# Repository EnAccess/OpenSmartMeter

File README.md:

<p align="center">
  
</p>
<p align="center">
    <em>The Open Smart Meter solves a problem that affects most solar developers in the industry. This inexpensive and open source Smart Meter meets IEC and key elements of the local regulations in Nigeria.</em>
</p>
<p align="center">

</p>

---

## Description

This repository contains manufacturing details as related to smart energy meter, details such as hardware design, web software, firmware, exterior casing STL files, rationale behing design, how-to document to guide a skilled user to replicate every part of the smart meter is available in the repository.

## Technical developmental breakdown

The open-source smart meter development has four main parts to it as highlighted below:

### Circuit and Enclosure Design

The circuit was designed on Kicad free and open-source PCB design software while the enclosure design was done using Fusion 360 software.

### PCB and Enclosure fabrication

PCB fabrication involves putting together the physical components that makes up the smart meter.
The PCB features a 2layer design incorporating CICADA GSM module for communication while the enclosure offers a minimalistic IP 51 design according to IEC metering enclosure design standard.

### Firmware, Web interface Development & API integration

The firmware code was written in Arduino IDE using C++, while the web front end was written majorly in HTML and CSS while the back end was written majorly in PHP.
Links to all these codes are here.
ThingsBoard API was used to view meter parameters such as energy, credit.

### Calibration & Testing

After putting the hardware and software together, we needed to validate the performance of the smart meter and ascertain its accuracy.
Due to varying tolerances of used components, it is vital to perform a calibration exercise.
This is used to correct any errors due to varying tolerances.
Further details including source code, schematics, and manufacturing files can be found in the EnAccess github repository

### Infrastructure diagram

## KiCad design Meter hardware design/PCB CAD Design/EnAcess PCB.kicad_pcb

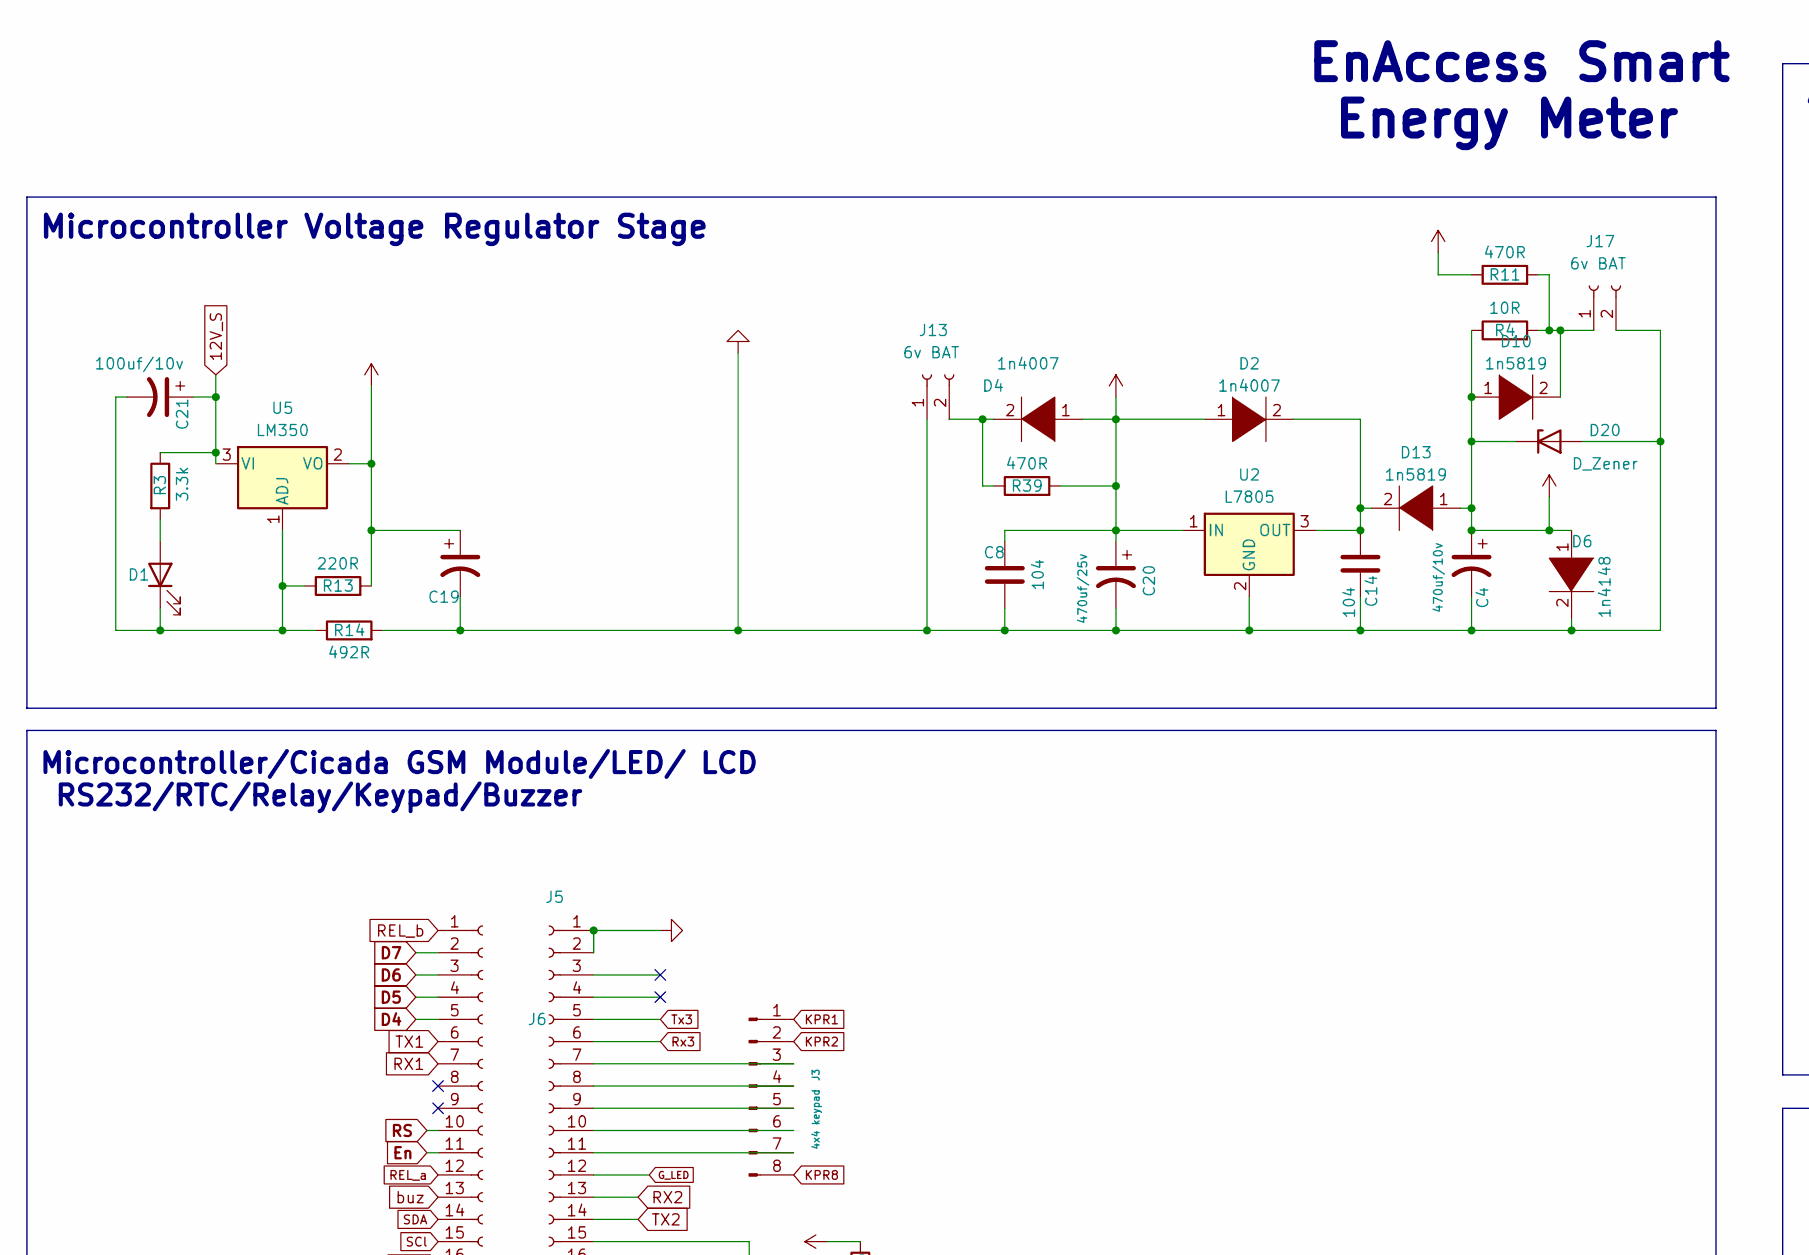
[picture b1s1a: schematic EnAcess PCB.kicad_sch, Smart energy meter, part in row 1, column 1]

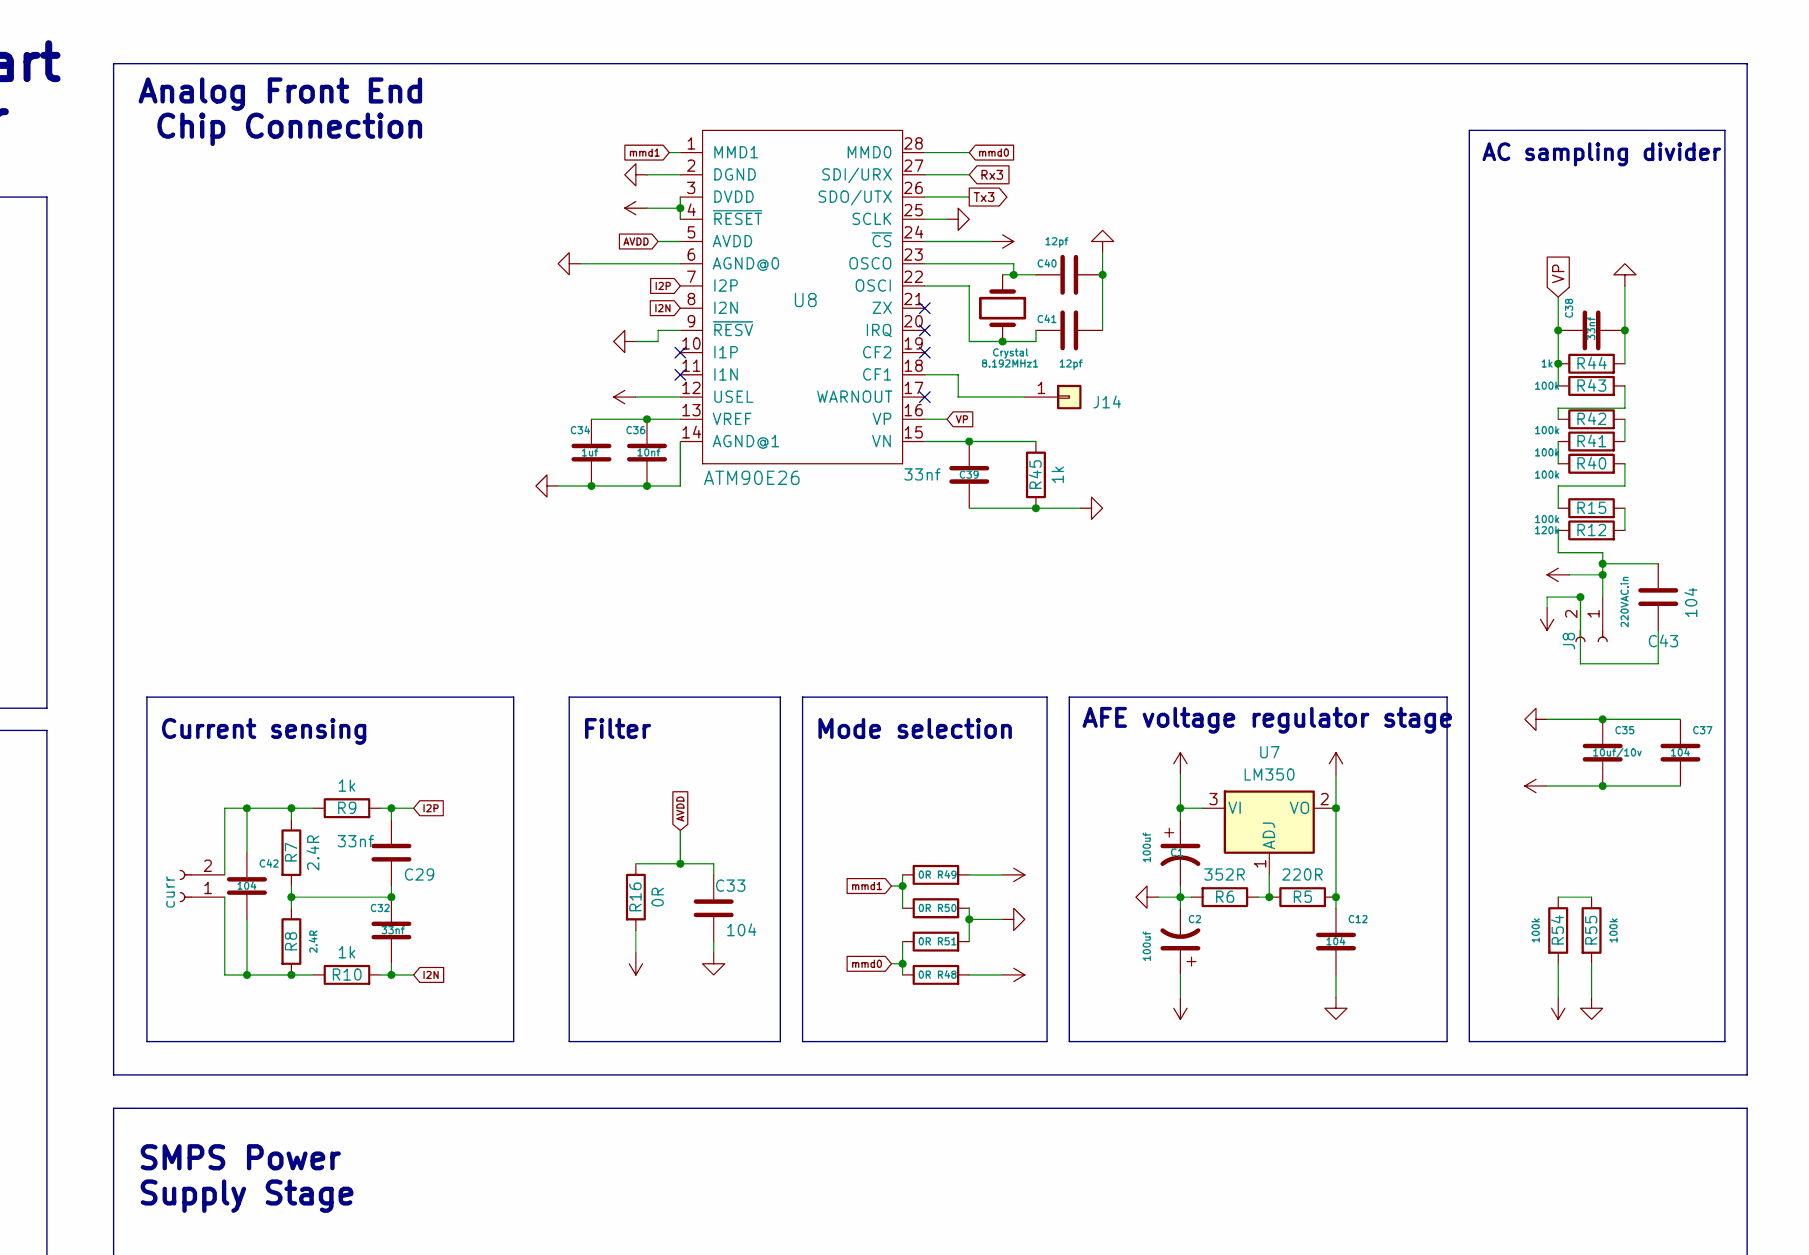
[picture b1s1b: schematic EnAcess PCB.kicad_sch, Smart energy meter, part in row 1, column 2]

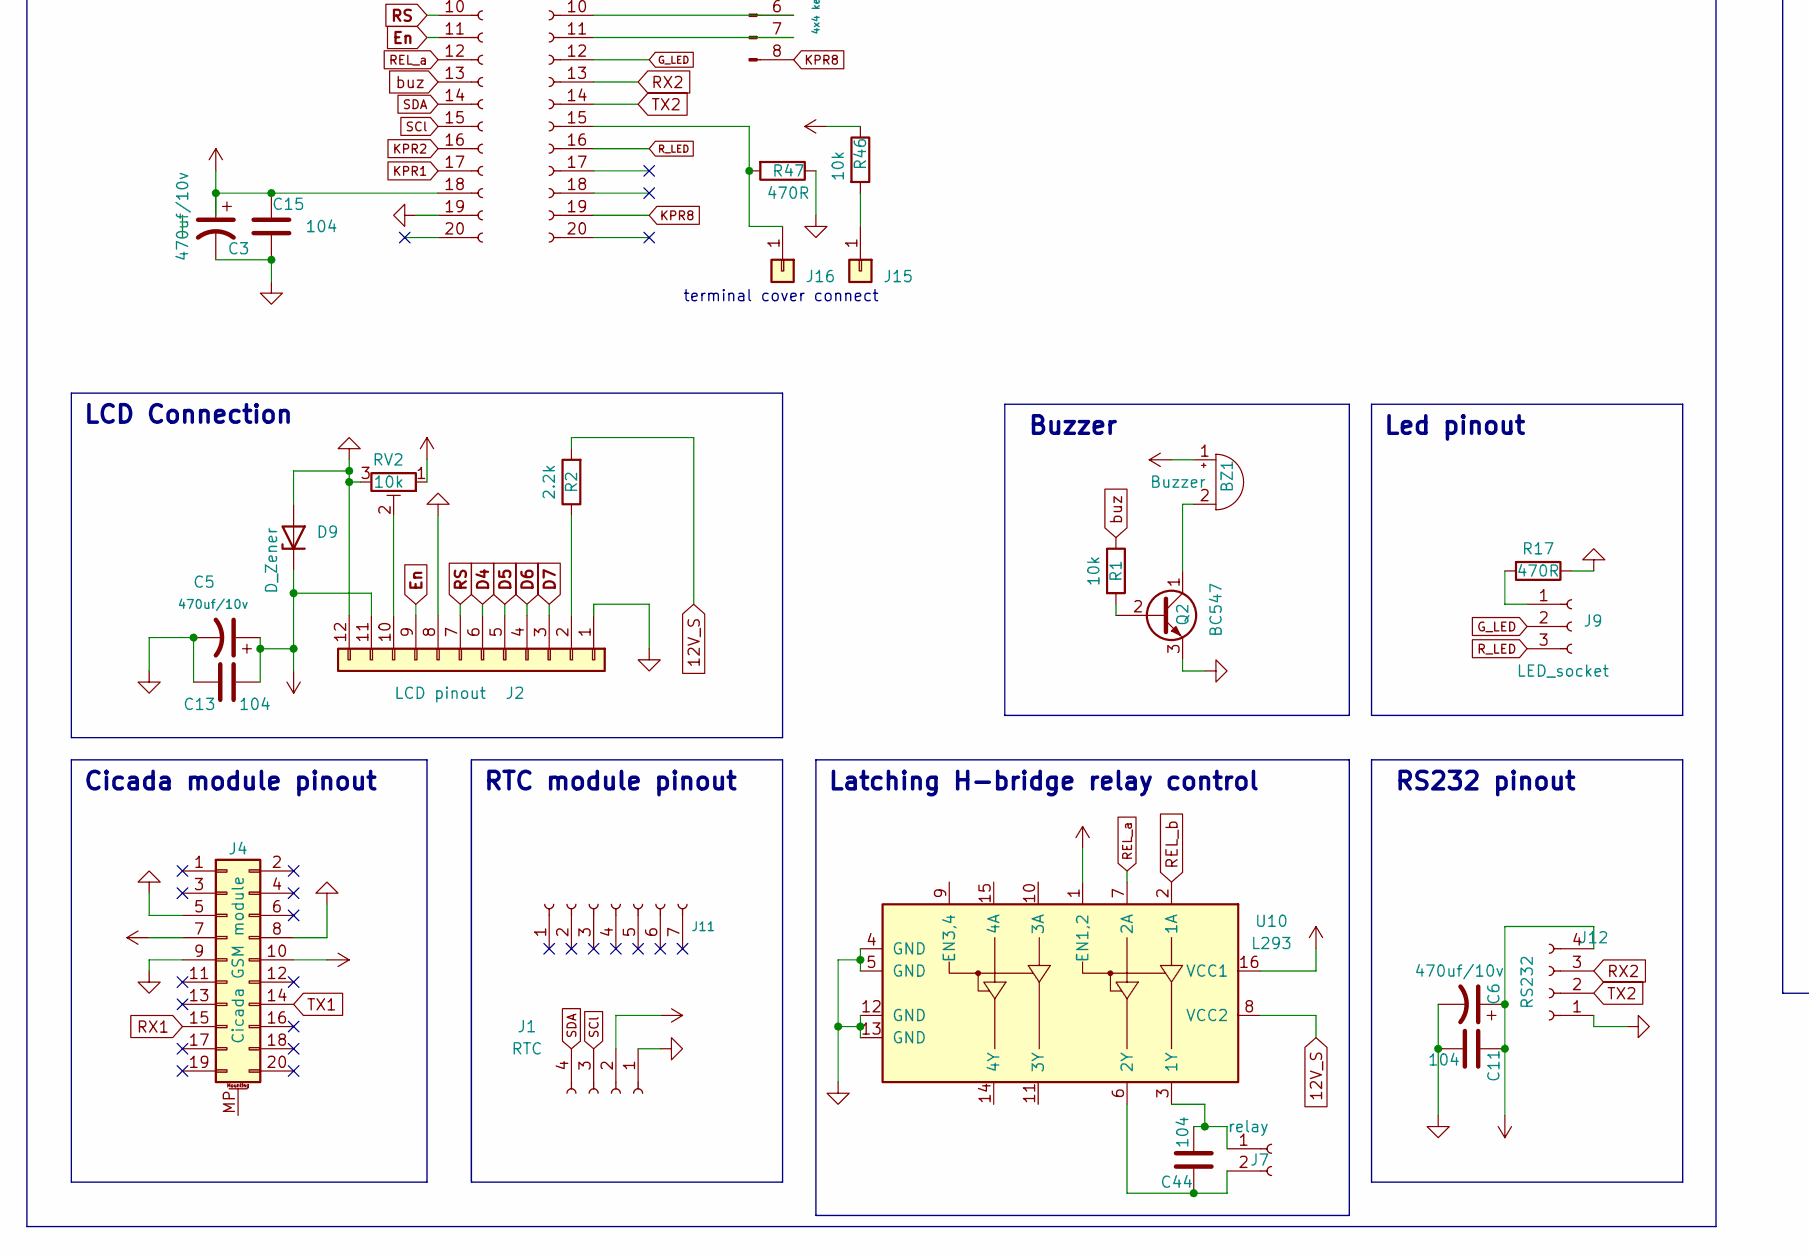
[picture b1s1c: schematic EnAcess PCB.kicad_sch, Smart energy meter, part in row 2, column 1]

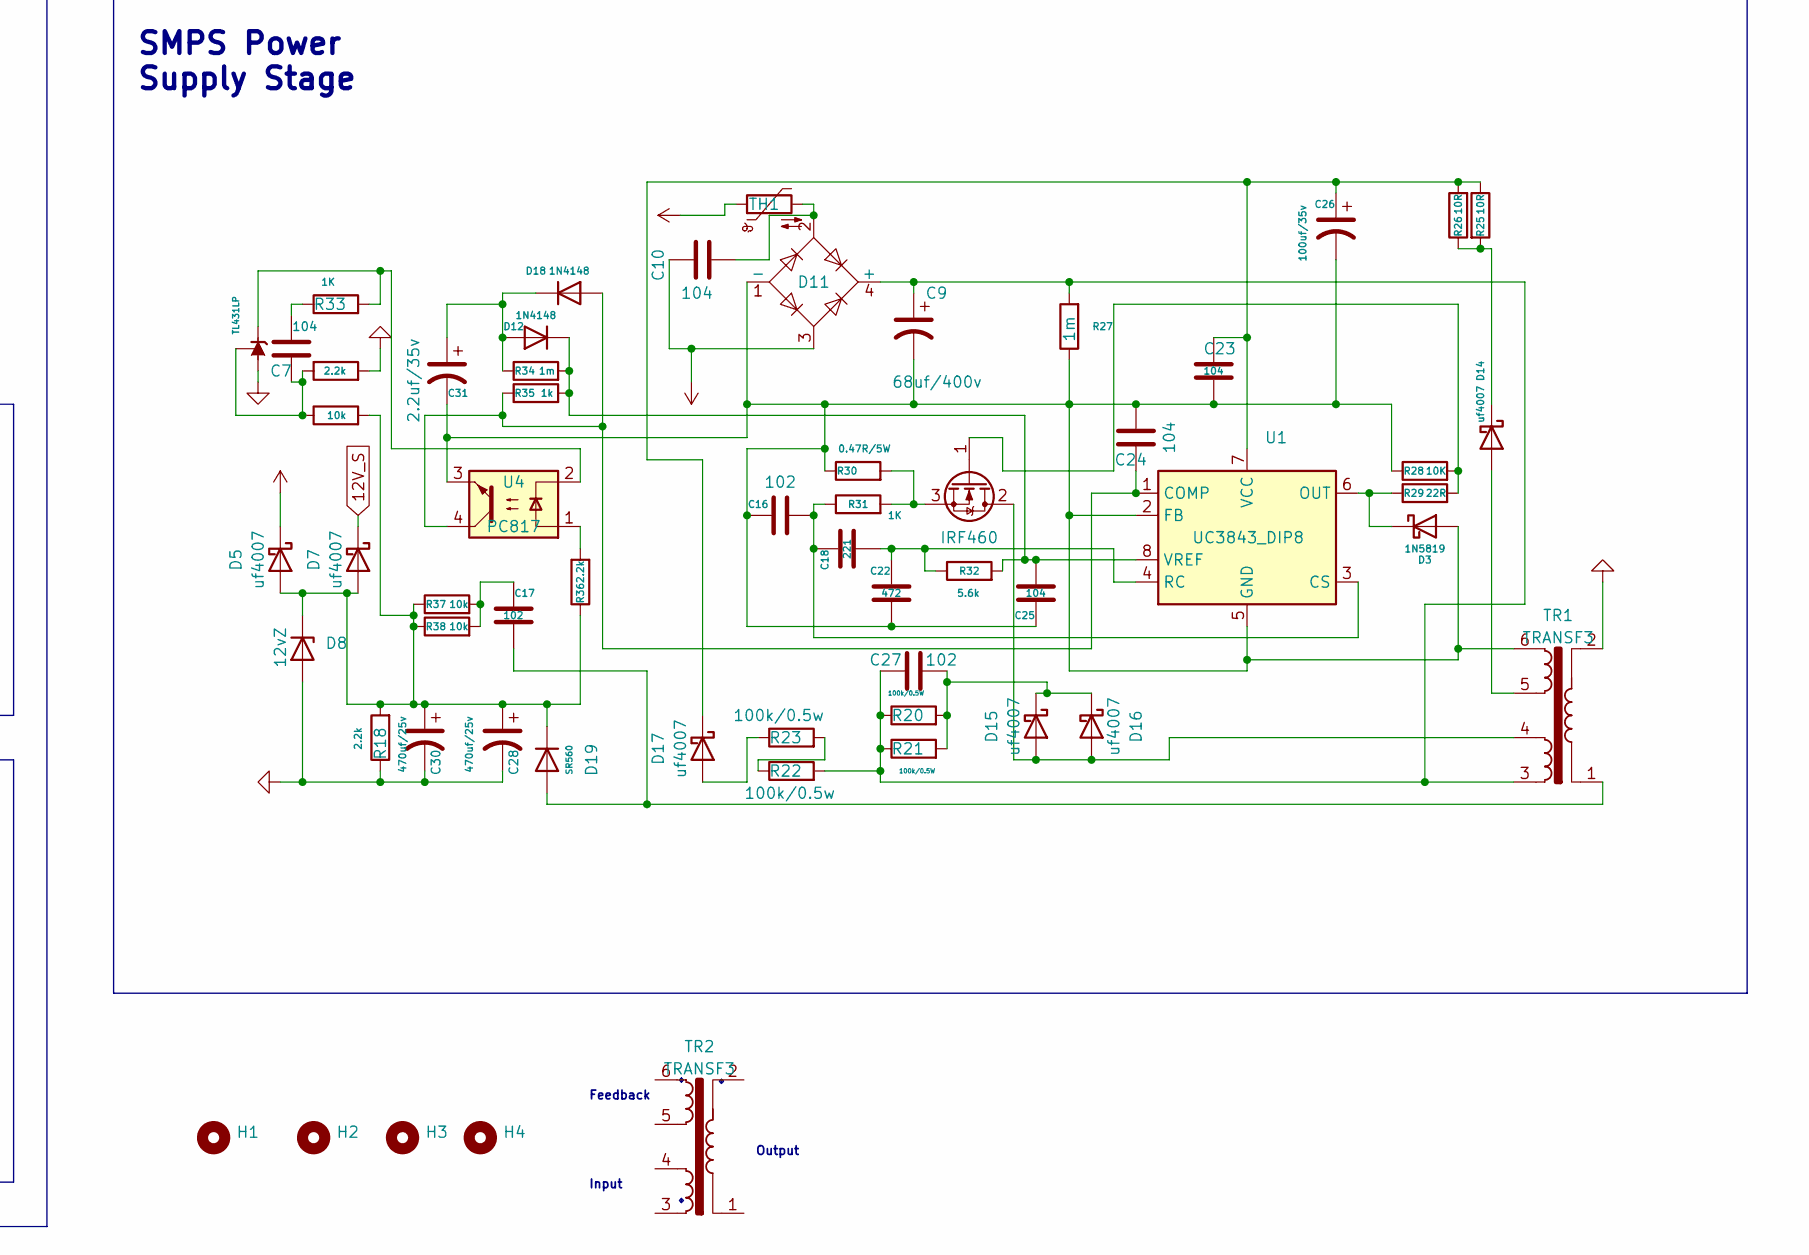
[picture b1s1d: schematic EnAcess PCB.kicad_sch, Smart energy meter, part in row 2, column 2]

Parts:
8.192MHz1: Crystal; Crystal_HC18-U_Vertical
BZ1: Buzzer; Buzzer_12x9.5RM7.6
C1, C2: 100uf; CP_Radial_D5.0mm_P2.50mm
C3: 470uf/10v; CP_Radial_D10.0mm_P4mm
C4: 470uf/10v; CP_Radial_D10.0mm_P5.00mm
C5, C6: 470uf/10v; CP_Radial_D10.0mm_P2.50mm
C7, C8, C11, C12, C13, C14, C15, C23, C24, C25, C33, C37, C42, C44: 104; C_Disc_D10.0mm_W2.5mm_P5.00mm
C9: 68uf/400v; CP_Radial_D17.0mm_P7.50mm
C10, C43: 104; C_Rect_L16.5mm_W5.0mm_P15.00mm_MKT
C16, C17, C27: 102; C_Disc_D10.0mm_W2.5mm_P5.00mm
C18: 221; C_Disc_D10.0mm_W2.5mm_P5.00mm
C19: CP_Radial_D5.0mm_P2.50mm
C20: 470uf/25v; CP_Radial_D10.0mm_P5.00mm
C21: 100uf/10v; CP_Radial_D5.0mm_P2.50mm
C22: 472; C_Disc_D10.0mm_W2.5mm_P5.00mm
C26: 100uf/35v; CP_Radial_D6.3mm_P2.50mm
C28, C30: 470uf/25v; CP_Radial_D8.0mm_P5.00mm
C29, C32, C38, C39: 33nf; C_Disc_D10.0mm_W2.5mm_P5.00mm
C31: 2.2uf/35v; CP_Radial_D5.0mm_P2.50mm
C34: 1uf; C_Disc_D10.0mm_W2.5mm_P5.00mm
C35: 10uf/10v; CP_Radial_D4.0mm_P1.50mm
C36: 10nf; C_Disc_D10.0mm_W2.5mm_P5.00mm
C40, C41: 12pf; C_Disc_D10.0mm_W2.5mm_P5.00mm
D1: LED_D3.0mm_FlatTop
D2, D4: 1n4007; D_DO-34_SOD68_P7.62mm_Horizontal
D3: 1N5819; D_DO-41_SOD81_P10.16mm_Horizontal
D5, D7, D14, D15, D16, D17: uf4007; D_DO-41_SOD81_P10.16mm_Horizontal
D6: 1n4148; D_DO-34_SOD68_P7.62mm_Horizontal
D8: 12vZ; D_DO-41_SOD81_P10.16mm_Horizontal
D9, D20: D_Zener; D_A-405_P12.70mm_Horizontal
D10, D13: 1n5819; D_DO-34_SOD68_P7.62mm_Horizontal
D11: Diode_Bridge_19.0x3.5x10.0mm_P5.0mm
D12, D18: 1N4148; D_DO-35_SOD27_P7.62mm_Horizontal
D19: SR560; D_DO-27_P15.24mm_Horizontal
H1, H2, H3, H4: MountingHole; MountingHole_3.2mm_M3_ISO14580_Pad_TopBottom
J1: RTC; PinSocket_1x04_P2.54mm_Vertical
J2: LCD pinout; JST_EH_S12B-EH_1x12_P2.50mm_Horizontal
J3: 4x4 keypad; PinHeader_1x08_P2.54mm_Vertical
J4: Cicada GSM module; PinHeader_2x10_P2.54mm_Vertical
J5, J6: PinSocket_1x20_P2.54mm_Vertical
J7: relay; JST_EH_S2B-EH_1x02_P2.50mm_Horizontal
J8: 220VAC.in; JST_EH_S2B-EH_1x02_P2.50mm_Horizontal
J9: LED_socket; JST_EH_B3B-EH-A_1x03_P2.50mm_Vertical
J10: curr; JST_EH_S2B-EH_1x02_P2.50mm_Horizontal
J11: PinSocket_1x07_P2.54mm_Vertical
J12: RS232; PinSocket_1x04_P2.54mm_Vertical
J13, J17: 6v BAT; JST_EH_S2B-EH_1x02_P2.50mm_Horizontal
J14, J15, J16: Conn_01x01; SolderWire-0.1sqmm_1x01_D0.4mm_OD1mm
Q2: BC547; TO-92_Inline_Wide
Q3: IRF460; TO-218-3_Vertical
R1, R24, R37, R38, R46: 10k; R_Axial_DIN0207_L6.3mm_D2.5mm_P10.16mm_Horizontal
R2, R19, R36: 2.2k; R_Axial_DIN0207_L6.3mm_D2.5mm_P10.16mm_Horizontal
R3: 3.3k; R_Axial_DIN0207_L6.3mm_D2.5mm_P10.16mm_Horizontal
R4, R25, R26: 10R; R_Axial_DIN0207_L6.3mm_D2.5mm_P10.16mm_Horizontal
R5, R13: 220R; R_Axial_DIN0207_L6.3mm_D2.5mm_P10.16mm_Horizontal
R6: 352R; R_Axial_DIN0207_L6.3mm_D2.5mm_P10.16mm_Horizontal
R7, R8: 2.4R; R_Axial_DIN0207_L6.3mm_D2.5mm_P10.16mm_Horizontal
R9, R10, R35, R44, R45: 1k; R_Axial_DIN0207_L6.3mm_D2.5mm_P10.16mm_Horizontal
R11, R17, R39, R47: 470R; R_Axial_DIN0207_L6.3mm_D2.5mm_P10.16mm_Horizontal
R12: 120k; R_Axial_DIN0207_L6.3mm_D2.5mm_P10.16mm_Horizontal
R14: 492R; R_Axial_DIN0207_L6.3mm_D2.5mm_P10.16mm_Horizontal
R15, R40, R41, R42, R43, R54, R55: 100k; R_Axial_DIN0207_L6.3mm_D2.5mm_P10.16mm_Horizontal
R16: 0R; R_Axial_DIN0207_L6.3mm_D2.5mm_P10.16mm_Horizontal
R18: 2.2k; R_Axial_DIN0614_L14.3mm_D5.7mm_P20.32mm_Horizontal
R20, R21: 100k/0.5W; R_Axial_DIN0207_L6.3mm_D2.5mm_P10.16mm_Horizontal
R22, R23: 100k/0.5w; R_Axial_DIN0207_L6.3mm_D2.5mm_P10.16mm_Horizontal
R27, R34: 1m; R_Axial_DIN0207_L6.3mm_D2.5mm_P10.16mm_Horizontal
R28: 10K; R_Axial_DIN0207_L6.3mm_D2.5mm_P10.16mm_Horizontal
R29: 22R; R_Axial_DIN0207_L6.3mm_D2.5mm_P10.16mm_Horizontal
R30: 0.47R/5W; R_Axial_DIN0922_L20.0mm_D9.0mm_P25.40mm_Horizontal
R31, R33: 1K; R_Axial_DIN0207_L6.3mm_D2.5mm_P10.16mm_Horizontal
R32: 5.6k; R_Axial_DIN0207_L6.3mm_D2.5mm_P10.16mm_Horizontal
R48, R49, R50, R51: 0R; R_0603_1608Metric
RV2: 10k; Potentiometer_Piher_PT-10-V05_Vertical
TH1: C_Disc_D9.0mm_W2.5mm_P5.00mm
TR1, TR2: TRANSF3; Transformer_CHK_EI30-2VA_2xSec
U1: UC3843_DIP8; DIP-8_W7.62mm
U2: L7805; TO-220-3_Vertical
U4: PC817; DIP-4_W7.62mm
U5, U7: LM350; TO-220-3_Vertical
U6: TL431LP; TO-92_Inline_Wide
U8: ATM90E26; SSOP-28_5.3x10.2mm_P0.65mm
U10: L293; DIP-16_W7.62mm

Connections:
12V_S: C21.1, D7.1 (K), R2.2, R3.1, U5.3 (VI), U10.8 (VCC2)
+3V3: C2.1, C12.1, C35.2, C37.2, R5.2, R16.2, R48.2, R49.2, U7.2 (VO), U8.3 (DVDD), U8.4 (~RESET), U8.12 (USEL), U8.24 (~CS)
+4V: C19.1, J4.10, R13.2, U5.2 (VO)
+12V: BZ1.1 (-), C1.1, C8.1, C20.1, D2.1 (K), D4.1 (K), D5.1 (K), R11.1, R39.2, R46.1, U2.1 (IN), U7.3 (VI)
AVDD: C33.1, R16.1, U8.5 (AVDD)
D4: J2.6, J6.5
D5: J2.5, J6.4
D6: J2.4, J6.3
D7: J2.3, J6.2
En: J2.9, J6.11
GND: C1.2, C2.2, C3.2, C4.2, C5.2, C6.2, C8.2, C11.2, C12.2, C13.2, C14.2, C15.2, C19.2, C20.2, C28.2, C30.2, C33.2, C34.2, C35.1, C36.2, C37.1, C38.2, C39.2, C40.2, C41.1, D6.2 (A), D8.2 (A), D9.2 (A), D20.2 (A), J1.1, J2.1, J2.8, J2.12, J4.5, J4.8, J4.9, J5.1, J5.2, J6.19, J12.1, J13.1, J17.2, Q2.3 (E), R6.2, R14.2, R17.1, R18.1, R19.2, R44.2, R45.2, R47.1, R50.2, R51.2, R55.2, RV2.3, TR1.2, U2.2 (GND), U6.2 (A), U8.2 (DGND), U8.6 (AGND@0), U8.9 (~RESV), U8.14 (AGND@1), U8.25 (SCLK), U10.4 (GND), U10.5 (GND), U10.12 (GND), U10.13 (GND)
G_LED: J5.12, J9.2
I2N: C32.2, R10.2, U8.8 (I2N)
I2P: C29.1, R9.2, U8.7 (I2P)
KPR1: J3.1, J6.17
KPR2: J3.2, J6.16
KPR8: J3.8, J5.19
LINE: C10.1, C43.2, D11.3, J8.1, R12.1
NEUT: C43.1, J8.2, R54.2, TH1.1
unnamed: BZ1.2 (+), Q2.1 (C)
unnamed: C7.1, R33.1
unnamed: C10.2, D11.2, TH1.2
unnamed: C17.1, R37.2, R38.2
unnamed: C29.2, C32.1, R7.2, R8.1
unnamed: D1.2 (A), R3.2
unnamed: C21.2, D1.1 (K), R13.1, R14.1, U5.1 (ADJ)
unnamed: D3.1 (K), R29.1, U1.6 (OUT)
unnamed: D4.2 (A), J13.2, R39.1
unnamed: D10.2 (A), J17.1, R4.2, R11.2
unnamed: C9.1, C27.1, D11.4 (+), R20.1, R21.1, R22.2, R27.2, TR1.3
unnamed: C9.2, C16.1, C22.2, C23.2, C24.1, C25.2, C26.2, C31.2, D3.2 (A), D11.1 (-), R27.1, R28.1, R30.1, TR1.6, U1.2 (FB), U1.5 (GND), U4.3
unnamed: C31.1, D12.2 (A), D18.1 (K), R34.1
unnamed: C25.1, D12.1 (K), R32.2, R34.2, R35.2, U1.8 (VREF)
unnamed: D14.2 (A), TR1.5
unnamed: D14.1 (K), R25.2, R26.1
unnamed: D15.2 (A), D16.2 (A), Q3.2 (D), TR1.4
unnamed: C27.2, D15.1 (K), D16.1 (K), R20.2, R21.2
unnamed: D17.2 (A), R23.1
unnamed: C23.1, C26.1, D17.1 (K), R25.1, R26.2, U1.7 (VCC)
unnamed: C24.2, D18.2 (A), R35.1, U1.1 (COMP), U4.4
unnamed: C17.2, D19.2 (A), TR1.1
unnamed: C28.1, C30.1, D5.2 (A), D7.2 (A), D8.1 (K), D19.1 (K), R18.2, R24.2, R36.1, R37.1, R38.1
unnamed: J2.2, R2.1
unnamed: J2.10, RV2.2
unnamed: J3.3, J5.7
unnamed: J3.4, J5.8
unnamed: J3.5, J5.9
unnamed: J3.6, J5.10
unnamed: J3.7, J5.11
unnamed: C44.2, J7.1, U10.3 (1Y)
unnamed: C44.1, J7.2, U10.6 (2Y)
unnamed: J9.1, R17.2
unnamed: C42.2, J10.1, R8.2, R10.1
unnamed: C42.1, J10.2, R7.1, R9.1
unnamed: J14.1, U8.18 (CF1)
unnamed: J15.1, R46.2
unnamed: J5.15, J16.1, R47.2
unnamed: Q2.2 (B), R1.2
unnamed: Q3.1 (G), R28.2, R29.2
unnamed: Q3.3 (S), R30.2, R31.2
unnamed: R12.2, R15.2
unnamed: R15.1, R40.2
unnamed: R22.1, R23.2
unnamed: R36.2, U4.1
unnamed: R40.1, R41.1
unnamed: R41.2, R42.2
unnamed: R42.1, R43.2
unnamed: R54.1, R55.1
unnamed: C16.2, C18.1, R31.1, U1.3 (CS)
unnamed: C18.2, C22.1, R32.1, U1.4 (RC)
unnamed: R33.2, U4.2, U6.3 (K)
unnamed: C7.2, R19.1, R24.1, U6.1 (REF)
unnamed: R5.1, R6.1, U7.1 (ADJ)
unnamed: 8.192MHz1.2, C41.2, U8.22 (OSCI)
unnamed: 8.192MHz1.1, C40.1, U8.23 (OSCO)
unnamed: C39.1, R45.1, U8.15 (VN)
unnamed: C34.1, C36.1, U8.13 (VREF)
REL_a: J6.12, U10.7 (2A)
REL_b: J6.1, U10.2 (1A)
RS: J2.7, J6.10
RX1: J4.15, J6.7
RX2: J5.13, J12.3
R_LED: J5.16, J9.3
Rx3: J5.6, U8.27 (SDI/URX)
SCl: J1.3, J6.15
SDA: J1.4, J6.14
TX1: J4.14, J6.6
TX2: J5.14, J12.2
Tx3: J5.5, U8.26 (SDO/UTX)
VP: C38.1, R43.1, R44.1, U8.16 (VP)
buz: J6.13, R1.1
mmd0: R48.1, R51.1, U8.28 (MMD0)
mmd1: R49.1, R50.1, U8.1 (MMD1)

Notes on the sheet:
Mode selection
AFE voltage regulator stage
Analog Front End Chip Connection
Latching H-bridge relay control
Led pinout
EnAccess Smart Energy Meter
LCD Connection
Feedback
AC sampling divider
Microcontroller/Cicada GSM Module/LED/ LCD RS232/RTC/Relay/Keypad/Buzzer
Current sensing
SMPS Power Supply Stage
RS232 pinout
Cicada module pinout
Buzzer
terminal cover connect
Output
RTC module pinout
Filter
Input
Microcontroller Voltage Regulator Stage

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
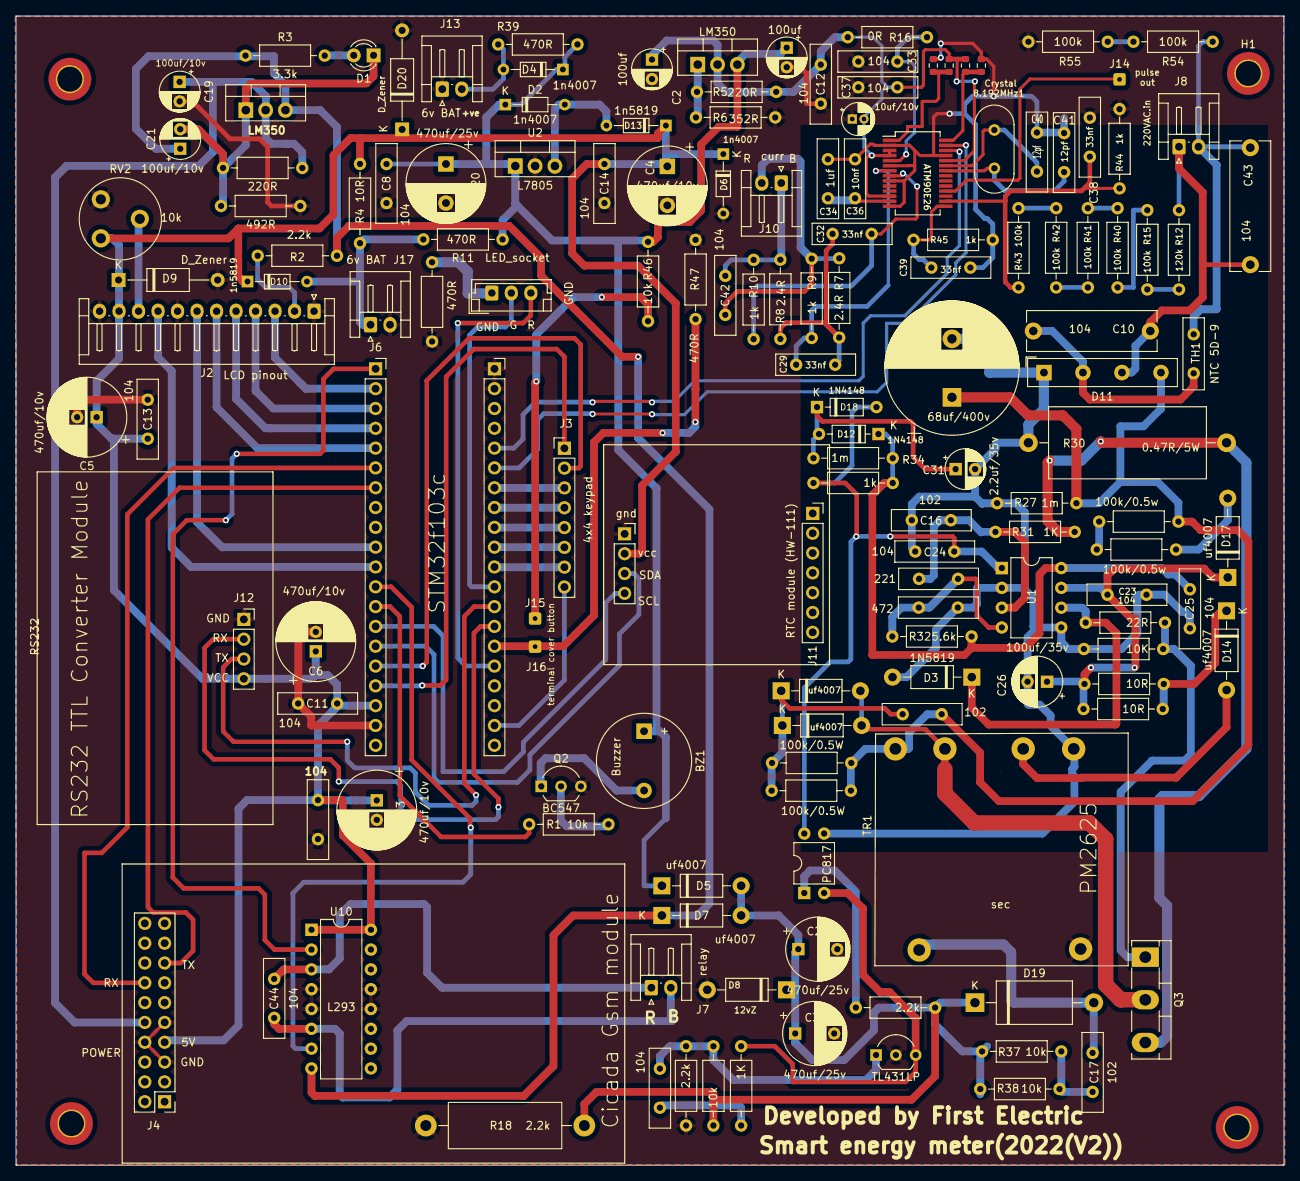
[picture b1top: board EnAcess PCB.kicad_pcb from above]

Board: 2 copper layers, 162.6 x 147.3 mm, 153 parts (0 on the bottom side), 95 nets.

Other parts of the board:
H1#2: MountingHole; MountingHole_3.2mm_M3_ISO14580_Pad_TopBottom

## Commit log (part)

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2023-05-24 Enable Latex (#67)
2023-05-31 Setup full `mkdocs` example
2023-05-31 PCB review (#8)
    * Delete EnAcess PCB.kicad_sch-bak
    * Delete Meter hardware design/PCB CAD Design directory
    * Create CAD
    * Add files via upload
    * Delete Meter hardware design/production file directory
    * Create pro
2023-05-31 Setup full `mkdocs` example (#69)
    * Setup full `mkdocs` example
    * Some more plugins
2023-05-31 Add `opaygp_decoder`
    From this commit: https://github.com/EnAccess/OpenPAYGO-HW/tree/875a013
2023-05-31 Exclude `lib/` from `clang-format`
2023-05-31 Update index.md with images
2023-05-31 Add API documentation
2023-05-31 Fix code
2023-06-05 Add `opaygo_decoder` (#71)
    * Add `opaygp_decoder`
    From this commit: https://github.com/EnAccess/OpenPAYGO-HW/tree/875a013
    * Exclude `lib/` from `clang-format`
    * Exclude `lib/` from EditorConfig checker
2023-06-06 STS and OpenPAYGO Token choice
2023-06-06 Choice between STS and OpenPAYGO
2023-06-07 Add something to documentation (#73)
    First paragraph from Firmware design
2023-06-09 Chore: Adding hardware documentation
2023-06-21 Chore: documented pcb-design, product specificaion and troubleshooting
2023-06-21 Apply Editor Config to entire repo
2023-06-21 Add Firmware design documentation
2023-06-21 Add Firmware design documentation (#76)
2023-06-22 Choice_between_STS_and_Openpaygo_final
2023-06-22 choice between STS and openpaygo Token, add unix_device and device_pa… (#72)
    * choice between STS and openpaygo Token, add unix_device and device_payg_logic and device_parameters
    * STS and OpenPAYGO Token choice
    * Choice between STS and OpenPAYGO
    * Choice between STS and OpenPAYGO with password and key combination
    * Choice_between_STS_and_Openpaygo_final
    ---------
2023-06-22 Chore: Upating mkdcs.yml
2023-06-28 Fix EditorConfig CI check
    Fixes:
    ```
    Could not get the ContentType of file: hardware
    stat hardware: no such file or directory
    Could not get the ContentType of file: design/
    stat design/: no such file or directory
2023-06-28 Fix Whitespaces
2023-06-28 Fix conversion artefacts in `pcd_design.md`
2023-06-28 Small improvements to `troubleshooting.md`
2023-06-28 Fix ThingsBoard references
2023-06-28 Fix **METERING CODE REF : 3**
2023-06-28 Fix tables
2023-06-28 Fix link and heading
2023-07-05 Add `index.md`
2023-07-05 Add `index.md` (#89)
2023-07-05 Add lessons learnt (#90)
    * Add `lessons-learnt.md`
2023-07-07 Update design.md
    important info to add!
2023-07-07 Update design.md (#95)
    important info to add!
2023-07-07 Update lessons-learnt.md (#96)
    spelling misstake
2023-07-07 Update api-documentation.md (#94)
2023-07-07 Revert "Update api-documentation.md (#94)"
    This reverts commit 3023593c55a9aedf43d6725cb5545ded935ee555.
2023-07-07 Revert "Update api-documentation.md (#94)" (#97)
    This reverts commit 3023593c55a9aedf43d6725cb5545ded935ee555.
2023-07-07 Revert "Update design.md (#95)"
    This reverts commit 1a51423dafcb9dbd6a33e20b0554a0ea1b340955.
2023-07-07 Revert "Update design.md (#95)" (#98)
    This reverts commit cfc15ecc7d392989445dbe7b134b66b39e1b1e46.
2023-07-17 git changes
2023-07-17 change on token_management
2023-07-17 main.cpp
2023-07-17 token_management
2023-07-17 add function GetDataFromToken from opaygo_decoder
2023-07-26 update branch
2023-07-28 add opaygo_functions
2023-07-28 complete main.cpp with functions of opaygo
2023-07-28 add UpdateDeviceStatusFromTokenValue()
2023-07-28 update code
2023-08-02 Test KiBot
2023-08-02 Add Google Analytics integration
2023-08-02 Add Google Analytics integration (#103)
2023-08-02 Adding cookie consent (#104)
2023-08-02 Update malformed Crystal reference (#105)
2023-08-02 Add KiCAD to `.gitignore`
2023-08-02 Upload KiBot output as artifact
2023-08-04 Minimal KiBot yaml
2023-08-04 Adjust PCB board thickness to 1.6
2023-08-05 solving problem of time
2023-08-11 clang-format problem solving
2023-08-11 EditConfig problem solving
2023-08-16 Adjust PCB board thickness to 1.6 (#110)
2023-08-16 Rename `Web Software` to `web_software`
2023-08-16 Update Github action
2023-08-16 Rename `Meter hardware design`
2023-08-16 Remove Whitespaces from folder structure (#112)
    * Rename `Web Software` to `web_software`
    * Rename `Firmware` and remove uneeded nesting
    * Update Github action
    * Rename `Meter hardware design`
    * Update Github Actions
2023-08-16 OpenPaygo Energy-based
2023-08-16 Move `energy_setpoint_calculator`
2023-08-16 Move the screen recording
2023-08-16 Move BOM to `production_files`
2023-08-16 Remove old PDF documentations
2023-08-16 Fix Screen Recording Demp
2023-08-16 update LoadActivationVariables()
2023-08-16 Rename files are restructure
2023-08-16 Format document
2023-08-19 changes after merge
2023-08-19 change #pragma once to #ifndef
2023-08-20 Move `ArduinoHttpClient` to where it is needed
2023-08-20 Remove uneeded `Wire.h`
2023-08-20 Update `RTClib`
2023-08-21 Opaygo step by step librairies and functions integration (#100)
    * git changes
    * Changes in loop
    * change on token_management
    * main.cpp
    * include opaygo_decoder
    * token_management
2023-08-21 Remove unneede `.gitignore`
2023-08-21 Reorder imports (#117)
2023-08-21 Upgrade libraries
    Mostly to silence warnings
2023-08-22 Simplify CI/CD setup (#120)
2023-08-22 Update comment
2023-08-23 Update `opaygo_decoder`
    Parity change to: https://github.com/EnAccess/OpenPAYGO-HW/pull/18
2023-08-23 Check for warnings in CI
2023-08-23 Remove leftover
2023-08-23 Enable `git-lfs` for step files
2023-08-23 Update KiCAD to use files
2023-08-23 Only apply `git-lfs` for PCB Design
2023-08-23 Test YouTube videos
2023-08-23 Add `Makefile` for convenience
2023-08-23 Store a sample render in repo
2023-08-24 Replace Demo with YouTube link
2023-08-30 edit enviroment for debug
2023-08-30 ignore PCB file backups
2023-08-30 Included Hardware self test and functional flowchart
2023-08-30 Restore state of `Choice-between-energy-based-and-time-based`
2023-08-30 Remove old `select_mode`
2023-08-30 Reorder to help git
2023-08-30 Revert unrelated changes
2023-08-31 Add ISR Callbacks
2023-09-06 Add all Diagrams
2023-09-07 Improve debug environment (#130)
2023-09-27 Integration of OpenPAYGO time-based functionnality
2023-10-05 Fix CI
2023-10-05 Check only `md`
2023-10-05 Improve failure
2023-10-05 Fix broken links in `README`
2023-10-05 Add firmware for device Self Test
2023-10-05 Change Github Actions order
2023-10-18 Refactoring of opaygo_functions
2023-10-18 formaat document
2023-10-18 Integration of open paygo time based fonctionality (#131)
    * Restore state of `Choice-between-energy-based-and-time-based`
    * upload_port
    * Integration of OpenPAYGO time-based functionnality
    * format document
    * deleting .gitignore
    ---------
2023-10-25 Add script to create custom OpenPAYGO tokens
2023-10-25 Revert changes to `lib`
2023-10-25 Whitespace changes
2023-10-27 Moved Getting Started documentation to quick-start-guide.md
2023-10-30 Refactor the Github Actions setup
2023-10-30 Fix Markdown lint
2023-10-30 Fix more Markdownlint
2023-10-30 One more
2023-10-30 Fix `yamllint`
2023-10-30 Fix shields
2023-10-31 Reformatting with Black tool
2023-10-31 Moved Excel sheet to documentation
2023-10-31 Lint
2023-11-02 Improve `.gitignore`
2023-11-07 Factory setting mode
2023-11-14 Factory setting mode (#140)
    * Factory setting mode
    * removing .gitignore
2023-11-14 Test_Procedure
2023-11-22 Update `README`
2023-11-23 Test `.editorconfig` simplification
    `.git` should be ignored by default
2023-11-23 DEBUG
2023-11-23 Test `.editorconfig` simplification (#143)
    * Test `.editorconfig` simplification
    `.git` should be ignored by default
    * DEBUG
    * Test
2023-11-28 Update `index.md`
2023-12-20 Revert "Factory setting mode (#140)"
    This reverts commit 36472224bf68d7266c0a5ee52bdc03a524dc1279.
2023-12-20 Revert "Factory setting mode (#140)" (#146)
    This reverts commit 36472224bf68d7266c0a5ee52bdc03a524dc1279.
2023-12-20 Revert "Refactoring of `opaygo_functions` (#138)" (#147)
    This reverts commit 2a9a94c72c56a5de6b4d8d05f925758101cc8f91.
2023-12-20 Revert "Integration of open paygo time based fonctionality (#131)"
    This reverts commit cc94c8e1b47413437fc9beac92128791ccecdfde.
2023-12-20 Revert "Improve debug environment (#130)"
    This reverts commit 06e76d202edb39b72279c3983a37d24a04065dc6.
2023-12-20 Revert "Improve debug environment (#130)" (#149)
    This reverts commit 06e76d202edb39b72279c3983a37d24a04065dc6.
2023-12-20 Revert "Reorder imports (#117)" (#150)
    This reverts commit 67e2c34736f4fb316f7ca69ac215391d00c420df.
2023-12-20 Revert "Remove unneede `.gitignore`"
    This reverts commit b689245f0b3dc2ebbe8be532ca701dacf87c6897.
2023-12-20 Revert "Revert "Reorder imports (#117)" (#150)" (#151)
    This reverts commit a8950b83d65669d33a8680edd053f09aec625cc8.
2023-12-20 Revert "Revert "Improve debug environment (#130)" (#149)"
    This reverts commit 5d4ed2b95feebe8a7a767ce452b9a87c37d15ec4.
2023-12-20 Revert "Revert "Integration of open paygo time based fonctionality (#131)" (#148)"
    This reverts commit 74e2c568938b736d4cb520d9e95af99399e02a2a.
2023-12-20 Revert "Revert "Integration of open paygo time based fonctionality (#131)" (#148)" (#153)
    This reverts commit 74e2c568938b736d4cb520d9e95af99399e02a2a.
2023-12-20 Revert "Revert "Refactoring of `opaygo_functions` (#138)" (#147)" (#154)
    This reverts commit 3c73f568f51a87098d6409cf9e82725f616384b7.
2023-12-20 Revert "Revert "Factory setting mode (#140)" (#146)"
    This reverts commit 90f874b599c006e68145160f30fc663075ec36ca.
2023-12-20 Renove unneeded `.gitignore`
2023-12-20 Renove unneeded `.gitignore` (#156)
2024-01-09 Update api-documentation.md (#158)
2024-01-10 Prepare support for multiple lessons learnt
2024-01-15 Add docusaurus site
2024-01-17 Format prettier
2024-01-19 Enable Google Analytics
2024-01-19 Rename folder
2024-01-19 Little clean up
2024-01-19 Re-order the Sidebar
2024-01-19 Fix ID clashes
2024-01-20 Simplify sidebar
2024-01-20 Add `.node-version` and update deploy
2024-01-22 Fix admontion
2024-01-22 Fix build docs
2024-01-22 Prettier
2024-01-22 Fix lint
2024-01-22 Add more ignores
2024-01-22 Init leftovers
2024-01-22 Add JavaScript linter
2024-01-22 Fix linter
2024-01-22 Revert test
2024-01-22 Add JavaScript linter (#161)
    * Add JavaScript linter
    * Fix linter
    * Remove left-over files
    * Revert test
2024-01-23 Don't explain the repo structure 5 times
2024-01-23 Add schematics overview
2024-01-23 Give logo background color
2024-01-23 Fix layer order
2024-01-23 Apply liniting to SVG
2024-01-23 Docu improvements (#162)
    * Remove leftover
    * Don't explain the repo structure 5 times
    * Add schematics overview
    * Prettify logo SVG
    * Give logo background color
    * Fix layer order
2024-01-23 Improvements to backend documentation
2024-01-23 Fix YouTube link
2024-01-23 Rename the Web Software guide
2024-01-23 Improve documentation even further (#163)
    * Create assembly guide
    * Improvements to backend documentation
    * Fix YouTube link
    * Update assembly guide
    * Rename the Web Software guide
2024-02-26 Update `yamllint`
2024-02-26 Oopsie
2024-02-26 More oopsie
2024-09-19 Add `CODE_OF_CONDUCT.md`
2024-09-23 Add `.github/SECURITY.md`
2024-09-23 Add `.github/ISSUE_TEMPLATE/config.yml`
2024-09-23 Add `.github/ISSUE_TEMPLATE/feature_request.yml`
2024-09-23 Add `CONTRIBUTING.md`
